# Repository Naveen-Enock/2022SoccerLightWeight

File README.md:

# 2022SoccerLightWeight

The soccer robot was built using fully custom 3d Printed Chassis and custom designed PCB's
Team Website:
https://eliterobotics.wixsite.com/teamelite

For more detailed information please check out our techincal paper:
https://docs.google.com/document/d/1pkVfc1k_Wh-xm2QmphN0Qvv6J-1zISbkPJ3Biad0Yy0/edit?usp=sharing

Our team is part or the **Princeton Soccer Robotics club**. This club consists of many other teams that also participate in the Robocup Junior Competition
https://soccer-robotics.github.io/psr/

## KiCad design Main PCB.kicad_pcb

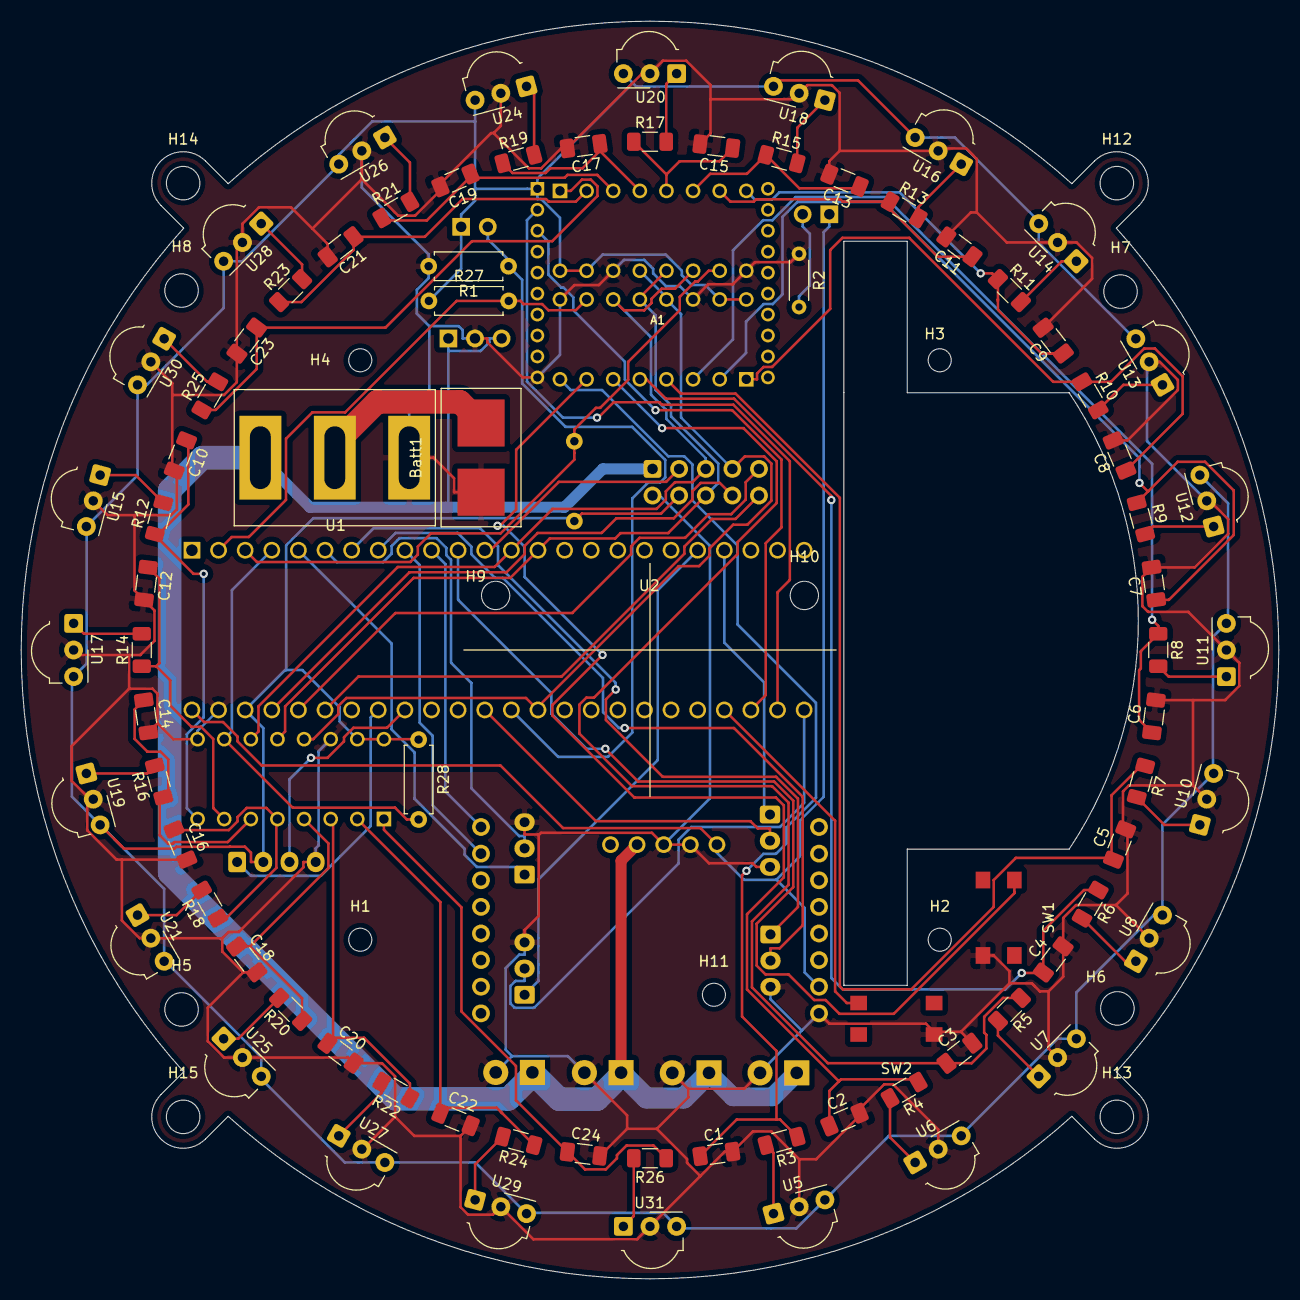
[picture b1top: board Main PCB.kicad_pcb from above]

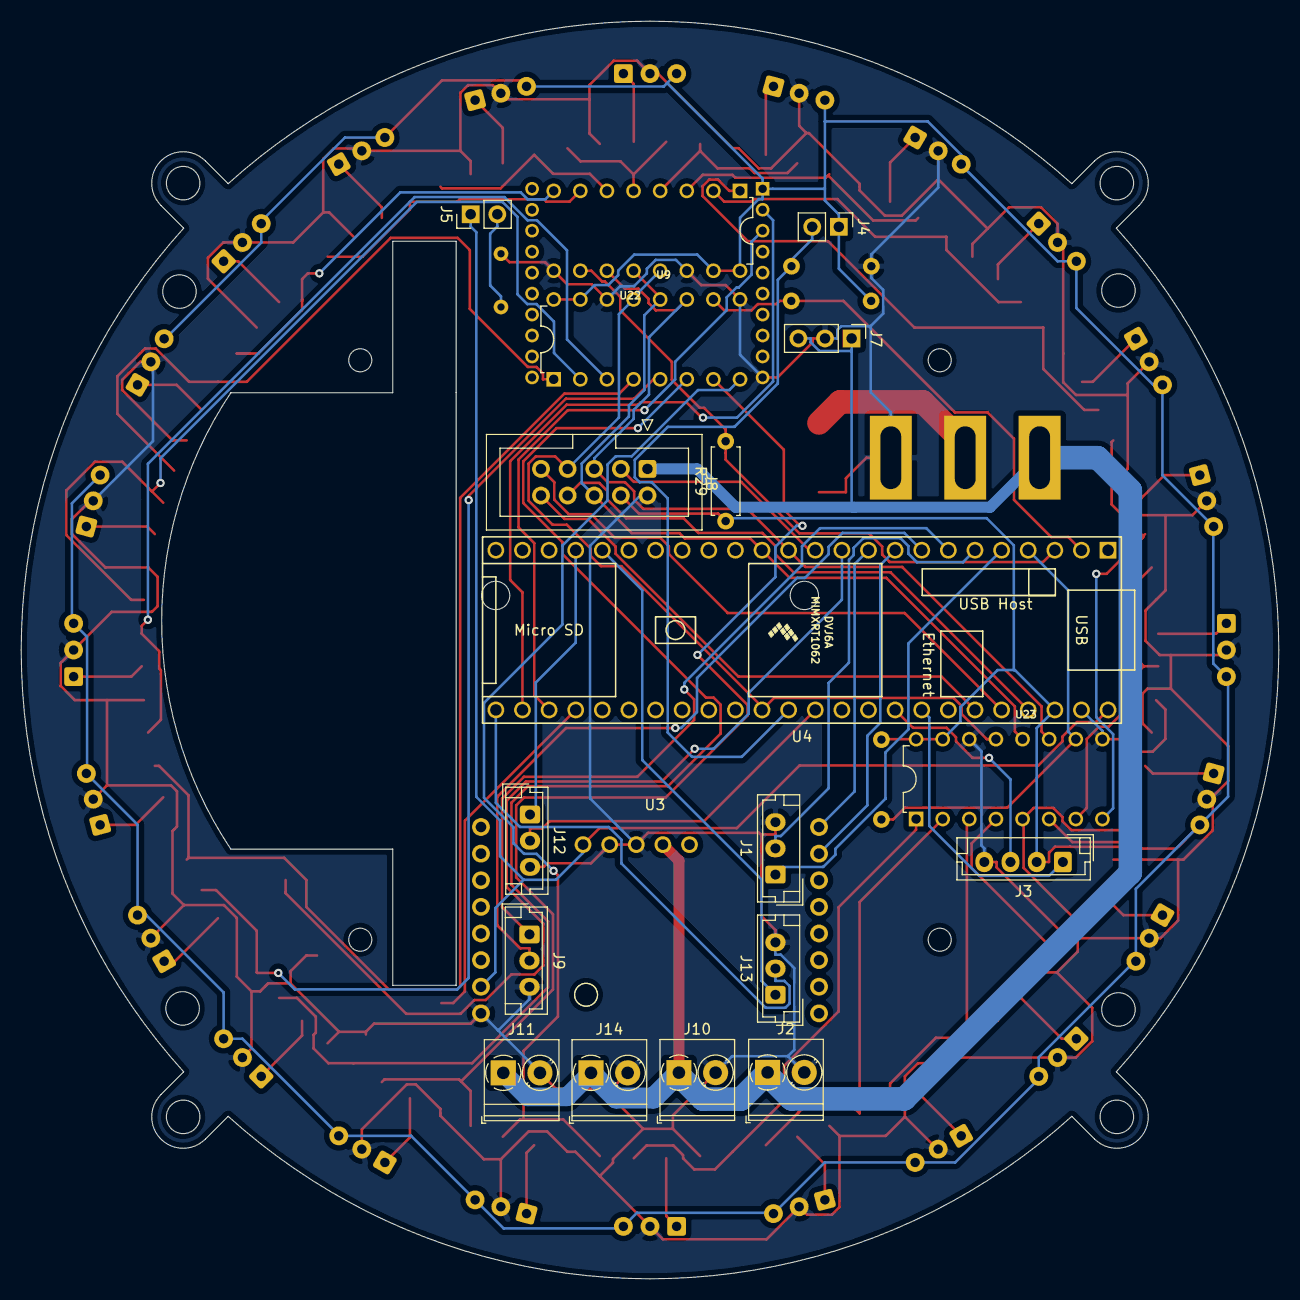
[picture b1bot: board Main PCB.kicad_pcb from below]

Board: 2 copper layers, 120.0 x 120.0 mm, 116 parts (19 on the bottom side), 81 nets.

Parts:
A1: XBee_THT; DIP-20
Batt1: 12V; PRT-11864
C1, C2, C3, C4, C5, C6, C7, C8, C9, C10, C11, C12, C13, C14, C15, C16, C17, C18, C19, C20, C21, C22, C23, C24: 0.1uF; C_1206_3216Metric_Pad1.33x1.80mm_HandSolder
H1, H2, H3, H4, H11: MountingHole; MountingHole_2.2mm_M2
H5, H6, H7, H8, H12, H13, H14, H15: MountingHole; MountingHole_3.2mm_M3
H9, H10: MountingHole; MountingHole_2.7mm_M2.5
J1, J9, J12, J13: Conn_01x03; JST_EH_B3B-EH-A_1x03_P2.50mm_Vertical
J2, J10, J11, J14: Screw_Terminal_01x02; TerminalBlock_Phoenix_PT-1,5-2-3.5-H_1x02_P3.50mm_Horizontal
J3: Conn_01x04; JST_EH_B4B-EH-A_1x04_P2.50mm_Vertical
J4, J5: Conn_01x02; PinHeader_1x02_P2.54mm_Vertical
J7: Conn_01x03; PinHeader_1x03_P2.54mm_Vertical
J8: Conn_01x10; IDC-Header_2x05_P2.54mm_Vertical
R1, R27, R28, R29: 10K; R_Axial_DIN0207_L6.3mm_D2.5mm_P7.62mm_Horizontal
R2: 220-1K; R_Axial_DIN0204_L3.6mm_D1.6mm_P5.08mm_Horizontal
R3, R4, R5, R6, R7, R8, R9, R10, R11, R12, R13, R14, R15, R16, R17, R18, R19, R20, R21, R22, R23, R24, R25, R26: 100k; R_1206_3216Metric_Pad1.30x1.75mm_HandSolder
SW1, SW2: SW_Push_Dual; TL3305CF260QG
U1: ADG417BN; Rocker Switch 20A
U2: OpenMV_Cam_H7_R2; OpenMV
U3: D24V25F5
U4: Teensy4.1; Teensy41
U5, U6, U7, U8, U10, U11, U12, U13, U14, U15, U16, U17, U18, U19, U20, U21, U24, U25, U26, U27, U28, U29, U30, U31: TSOP25xx; Vishay_MOLD-3Pin
U9, U22, U23: MCP3008; DIP16-2.54-19.2X7.62MM

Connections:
3.3V: A1.1, J3.2, J4.1, J8.4, R27.1, R28.1, R29.1, U4.46, U5.3, U6.3, U7.3, U8.3, U9.15, U9.16, U10.3, U11.3, U12.3, U13.3, U14.3, U15.3, U16.3, U17.3, U18.3, U19.3, U20.3, U21.3, U22.15, U22.16, U23.15, U23.16, U24.3, U25.3, U26.3, U27.3, U28.3, U29.3, U30.3, U31.3
5V: J5.1, U2.B7, U3.1, U4.48
12V: J2.1, J7.1, J7.3, J8.1, J10.1, J11.1, J14.1, U1.1, U3.4
GND: A1.10, Batt1.2, C1.2, C2.2, C3.2, C4.2, C5.2, C6.2, C7.2, C8.2, C9.2, C10.2, C11.2, C12.2, C13.2, C14.2, C15.2, C16.2, C17.2, C18.2, C19.2, C20.2, C21.2, C22.2, C23.2, C24.2, J1.3, J2.2, J3.4, J7.2, J8.2, J9.3, J10.2, J11.2, J12.3, J13.3, J14.2, R1.2, R2.1, SW1.3, SW2.2, U1.6, U2.B8, U3.2, U3.3, U4.47, U5.2, U6.2, U7.2, U8.2, U9.9, U9.14, U10.2, U11.2, U12.2, U13.2, U14.2, U15.2, U16.2, U17.2, U18.2, U19.2, U20.2, U21.2, U22.9, U22.14, U23.9, U23.14, U24.2, U25.2, U26.2, U27.2, U28.2, U29.2, U30.2, U31.2
Kicker: J8.3, U4.12
MISO: J8.6, U4.14, U9.12, U22.12, U23.12
MOSI: J8.5, U4.13, U9.11, U22.11, U23.11
unnamed: A1.2, U4.26
unnamed: A1.3, U4.27
unnamed: Batt1.1, U1.8
unnamed: C1.1, R3.1, U9.8
unnamed: C2.1, R4.1, U9.7
unnamed: C3.1, R5.1, U9.6
unnamed: C4.1, R6.1, U9.5
unnamed: C5.1, R7.1, U9.4
unnamed: C6.1, R8.1, U9.3
unnamed: C7.1, R9.1, U9.2
unnamed: C8.1, R10.1, U9.1
unnamed: C9.1, R11.1, U22.8
unnamed: C10.1, R12.1, U23.8
unnamed: C11.1, R13.1, U22.7
unnamed: C12.1, R14.1, U23.7
unnamed: C13.1, R15.1, U22.6
unnamed: C14.1, R16.1, U23.6
unnamed: C15.1, R17.1, U22.5
unnamed: C16.1, R18.1, U23.5
unnamed: C17.1, R19.1, U22.4
unnamed: C18.1, R20.1, U23.4
unnamed: C19.1, R21.1, U22.3
unnamed: C20.1, R22.1, U23.3
unnamed: C21.1, R23.1, U22.2
unnamed: C22.1, R24.1, U23.2
unnamed: C23.1, R25.1, U22.1
unnamed: C24.1, R26.1, U23.1
unnamed: J1.1, U4.5
unnamed: J1.2, U4.6
unnamed: J3.1, U4.41
unnamed: J3.3, U4.40
unnamed: J4.2, R1.1, U4.36
unnamed: J5.2, R2.2
unnamed: J8.8, U4.45
unnamed: J8.9, U4.44
unnamed: J8.10, U4.43
unnamed: J9.1, U4.7
unnamed: J9.2, U4.8
unnamed: J12.2, U4.37
unnamed: J13.2, U4.25
unnamed: R3.2, U5.1
unnamed: R4.2, U6.1
unnamed: R5.2, U7.1
unnamed: R6.2, U8.1
unnamed: R7.2, U10.1
unnamed: R8.2, U11.1
unnamed: R9.2, U12.1
unnamed: R10.2, U13.1
unnamed: R11.2, U14.1
unnamed: R12.2, U15.1
unnamed: R13.2, U16.1
unnamed: R14.2, U17.1
unnamed: R15.2, U18.1
unnamed: R16.2, U19.1
unnamed: R17.2, U20.1
unnamed: R18.2, U21.1
unnamed: R19.2, U24.1
unnamed: R20.2, U25.1
unnamed: R21.2, U26.1
unnamed: R22.2, U27.1
unnamed: R23.2, U28.1
unnamed: R24.2, U29.1
unnamed: R25.2, U30.1
unnamed: R26.2, U31.1
unnamed: R27.2, U4.2, U9.10
unnamed: R28.2, U4.4, U23.10
unnamed: R29.2, U4.3, U22.10
unnamed: SW1.2, U4.11
unnamed: SW2.3, U4.28
unnamed: U2.A1, U4.10
unnamed: U2.A2, U4.9
PWM1: J13.1, U4.20
PWM2: J12.1, U4.21
SCK1: J8.7, U4.35, U9.13, U22.13, U23.13

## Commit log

2022-04-02 initial
2022-04-02 code modified
2022-04-02 code optimized
2022-04-02 optomised code
2022-04-02 fixed angle
2022-04-02 added linesensor
2022-04-16 Ball positioning
2022-04-16 Orientation sensor initiallization
2022-04-16 Rotation Correction
2022-04-23 cam and line avoidance added
2022-04-23 Revert "cam and line avoidance added"
    This reverts commit b153eb7175778771fe030258283199450ebfa7a3.
2022-04-25 Revert "Revert "cam and line avoidance added""
    This reverts commit 1857bdaf6f4bae68d86b9dad2c324e34dd5aeb6a.
2022-04-26 Line Detection Algorithm
2022-04-28 Staying inside lines
2022-04-28 Commented linesensor since not using in main.cpp
2022-04-28 Moved line angle to constructor since the values are constant
2022-05-01 Making robot Score
2022-05-07 added kicker calculations
2022-05-21 final
2022-06-04 Before Worlds
2022-07-06 new dot product
2022-07-08 before travel
2022-07-11 word
2022-07-12 night before First competition day
2022-07-12 night Before first day
2022-07-15 finals morning
2022-07-23 Final again
2025-03-18 Added OpenMV File
